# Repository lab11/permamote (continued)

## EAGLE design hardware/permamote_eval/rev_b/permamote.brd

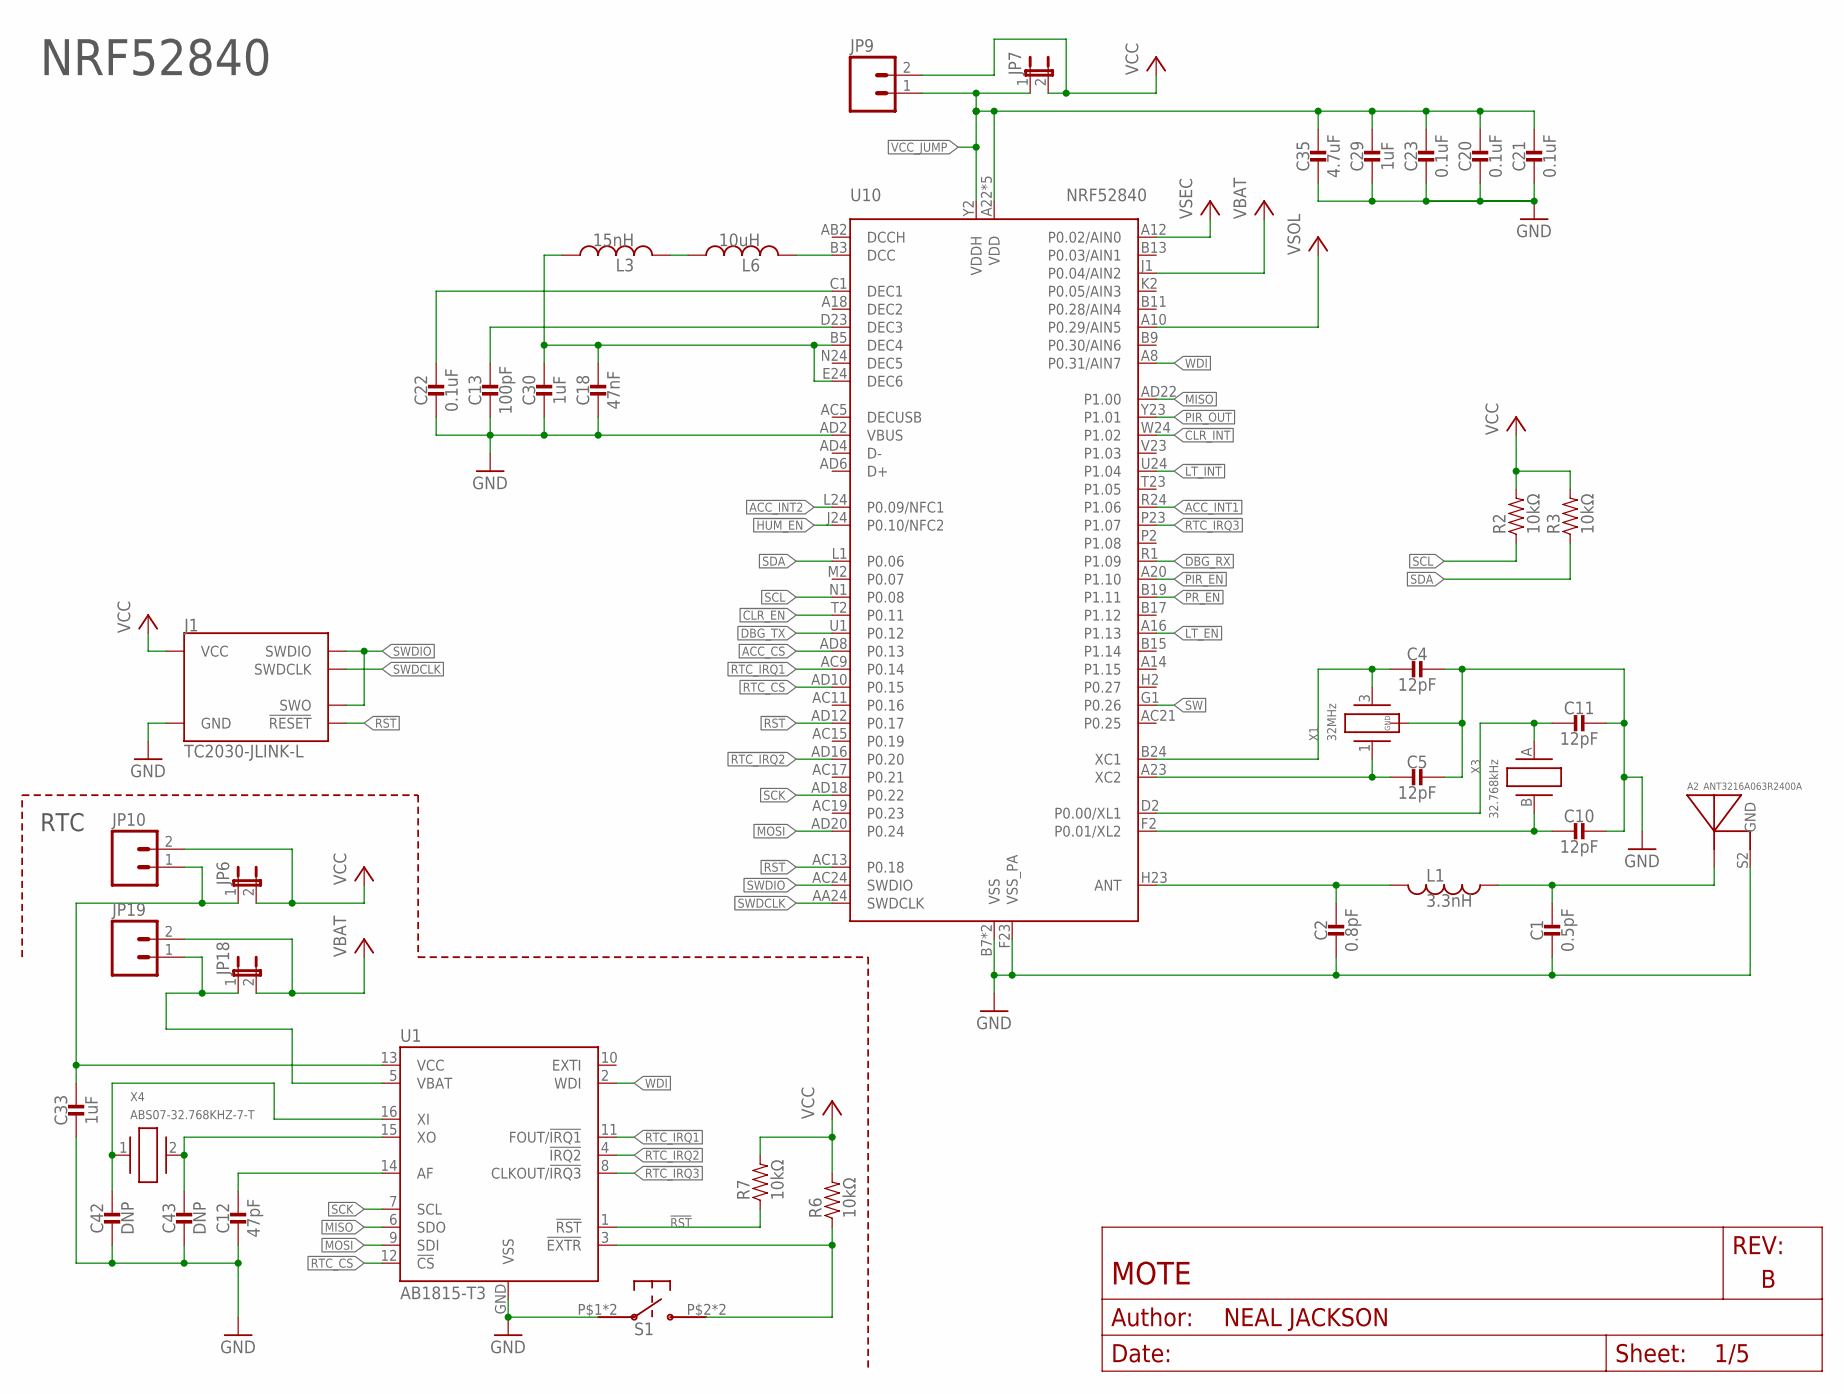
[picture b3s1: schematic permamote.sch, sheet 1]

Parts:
A2: ANT3216A063R2400A
C1: 0.5pF; 0402_CAP; DIGIKEY 490-6264-1-ND
C2: 0.8pF; 0402_CAP; DIGIKEY 490-6269-1-ND
C4, C5, C10, C11: 12pF; 0402_CAP; DIGIKEY 490-6197-1-ND
C12: 47pF; 0402_CAP; DIGIKEY 490-5942-1-ND
C13: 100pF; 0402_CAP; DIGIKEY 490-5922-1-ND
C18: 47nF; 0402_CAP; DIGIKEY 445-1264-1-ND
C20, C21, C22, C23: 0.1uF; 0402_CAP; DIGIKEY 490-6328-1-ND
C29, C30, C33: 1uF; 0402_CAP; DIGIKEY 490-7195-1-ND
C35: 4.7uF; 0402_CAP; DIGIKEY 445-5947-1-ND
C42, C43: DNP; 0402_CAP
J1: TC2030-JLINK-L; TC2030-IDC
JP6, JP7, JP18: JUMPER-2SMD-NC; SJ_2S
JP9, JP10, JP19: M02PTH; 1X02
L1: 3.3nH; 0402_CAP; DIGIKEY 535-10426-1-ND
L3: 15nH; 0402_CAP; DIGIKEY 587-1521-1-ND
L6: 10uH; 0603_CAP; DIGIKEY 490-4025-1-ND
R2, R3, R6, R7: 10kΩ; 0402_RES; DIGIKEY 311-10KJRCT-ND
S1: EVQP2
U1: AB1815-T3; QFN-16-3MM
U10: NRF52840; AQFN73
X1: 32MHz; TXC-7V
X3: 32.768kHz; ABS05
X4: ABS07-32.768KHZ-7-T; 2-SMD

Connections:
!CLR_EN: U10.T2 (P0.11); also elsewhere on the board
!CLR_INT: U10.W24 (P1.02); also elsewhere on the board
!HUM_EN: U10.J24 (P0.10/NFC2); also elsewhere on the board
!LT_EN: U10.A16 (P1.13); also elsewhere on the board
!LT_INT: U10.U24 (P1.04); also elsewhere on the board
!PIR_EN: U10.A20 (P1.10); also elsewhere on the board
!PR_EN: U10.B19 (P1.11); also elsewhere on the board
!RST: J1.3 (!RESET), R7.1, U1.1 (!RST), U10.AC13 (P0.18), U10.AD12 (P0.17); also elsewhere on the board
!RTC_EXTR: R6.1, S1.P$2, S1.P$4, U1.3 (!EXTR)
!RTC_IRQ1: U1.11 (FOUT/!IRQ1), U10.AC9 (P0.14); also elsewhere on the board
!RTC_IRQ2: U1.4 (!IRQ2), U10.AD16 (P0.20); also elsewhere on the board
!RTC_IRQ3: U1.8 (CLKOUT/!IRQ3), U10.P23 (P1.07); also elsewhere on the board
ACC_CS: U10.AD8 (P0.13); also elsewhere on the board
ACC_INT1: U10.R24 (P1.06); also elsewhere on the board
ACC_INT2: U10.L24 (P0.09/NFC1); also elsewhere on the board
DBG_RX: U10.R1 (P1.09); also elsewhere on the board
DBG_TX: U10.U1 (P0.12); also elsewhere on the board
GND: A2.S2 (GND), C1.2, C2.2, C4.1, C5.1, C10.1, C11.1, C12.2, C13.2, C18.2, C20.2, C21.2, C22.2, C23.2, C29.2, C30.2, C33.2, C35.2, C42.2, C43.2, J1.5 (GND), S1.P$1, S1.P$3, U1.GND (VSS), U10.AD2 (VBUS), U10.B7 (VSS), U10.F23 (VSS_PA), U10.GND (VSS), X1.2 (GND), X1.4 (GND); also elsewhere on the board
MISO: U1.6 (SDO), U10.AD22 (P1.00); also elsewhere on the board
MOSI: U1.9 (SDI), U10.AD20 (P0.24); also elsewhere on the board
unnamed: C22.1, U10.C1 (DEC1)
unnamed: C18.1, C30.1, L3.1, U10.B5 (DEC4), U10.E24 (DEC6)
unnamed: C13.1, U10.D23 (DEC3)
unnamed: C2.1, L1.2, U10.H23 (ANT)
unnamed: A2.S1 (ANTENNA), C1.1, L1.1
unnamed: C4.2, U10.B24 (XC1), X1.3 (2)
unnamed: C5.2, U10.A23 (XC2), X1.1
unnamed: C12.1, U1.14 (AF)
unnamed: C42.1, U1.16 (XI), X4.1
unnamed: C43.1, U1.15 (XO), X4.2
unnamed: C33.1, JP6.1, JP10.1, U1.13 (VCC)
unnamed: L6.2, U10.B3 (DCC)
unnamed: L3.2, L6.1
unnamed: JP18.1, JP19.1, U1.5 (VBAT)
PIR_OUT: U10.Y23 (P1.01); also elsewhere on the board
RTC_CS: U1.12 (!CS), U10.AD10 (P0.15); also elsewhere on the board
SCK: U1.7 (SCL), U10.AD18 (P0.22); also elsewhere on the board
SCL: R2.1, U10.N1 (P0.08); also elsewhere on the board
SDA: R3.1, U10.L1 (P0.06); also elsewhere on the board
SW: U10.G1 (P0.26); also elsewhere on the board
SWDCLK: J1.4 (SWDCLK), U10.AA24 (SWDCLK); also elsewhere on the board
SWDIO: J1.2 (SWDIO), J1.6 (SWO), U10.AC24 (SWDIO); also elsewhere on the board
VBAT: JP18.2, JP19.2, U10.J1 (P0.04/AIN2); also elsewhere on the board
VCC: J1.1 (VCC), JP6.2, JP7.2, JP9.2, JP10.2, R2.2, R3.2, R6.2, R7.2; also elsewhere on the board
VCC_JUMP: C20.1, C21.1, C23.1, C29.1, C35.1, JP7.1, JP9.1, U10.A22 (VDD), U10.AD14 (VDD), U10.AD23 (VDD), U10.B1 (VDD), U10.W1 (VDD), U10.Y2 (VDDH); also elsewhere on the board
VSEC: U10.A12 (P0.02/AIN0); also elsewhere on the board
VSOL: U10.A10 (P0.29/AIN5); also elsewhere on the board
WDI: U1.2 (WDI), U10.A8 (P0.31/AIN7); also elsewhere on the board
XL1: C11.2, U10.D2 (P0.00/XL1), X3.A (1)
XL2: C10.2, U10.F2 (P0.01/XL2), X3.B (2)

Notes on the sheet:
NRF52840
RTC

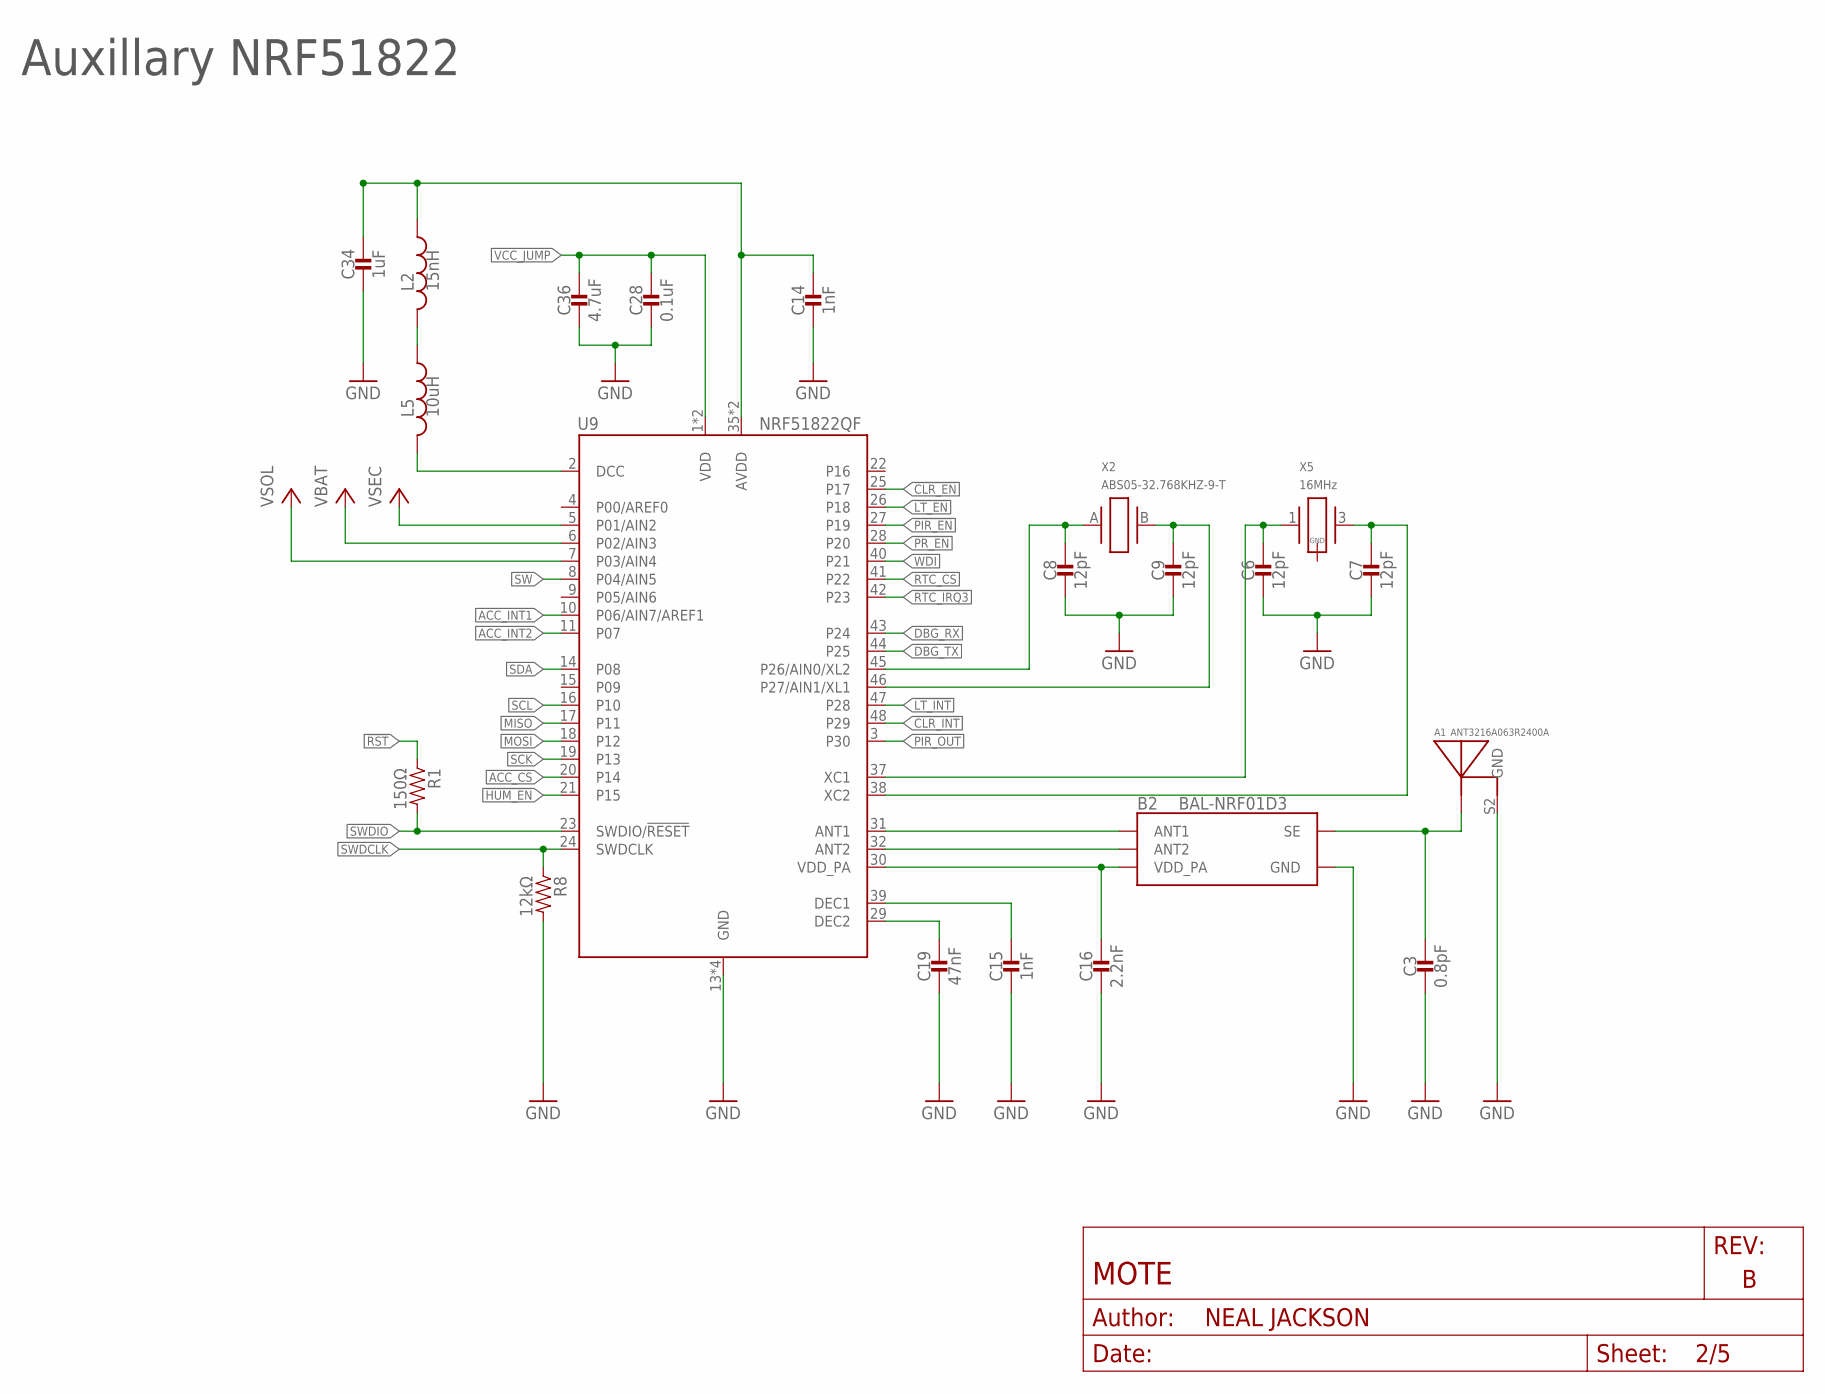
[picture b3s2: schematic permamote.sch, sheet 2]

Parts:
A1: ANT3216A063R2400A
B2: BAL-NRF01D3
C3: 0.8pF; 0402_CAP; DIGIKEY 490-6269-1-ND
C6, C7, C8, C9: 12pF; 0402_CAP; DIGIKEY 490-6197-1-ND
C14, C15: 1nF; 0402_CAP; DIGIKEY 490-1303-1-ND
C16: 2.2nF; 0402_CAP; DIGIKEY 490-5419-1-ND
C19: 47nF; 0402_CAP; DIGIKEY 445-1264-1-ND
C28: 0.1uF; 0402_CAP; DIGIKEY 490-6328-1-ND
C34: 1uF; 0402_CAP; DIGIKEY 490-7195-1-ND
C36: 4.7uF; 0402_CAP; DIGIKEY 445-5947-1-ND
L2: 15nH; 0402_CAP; DIGIKEY 587-1521-1-ND
L5: 10uH; 0603_CAP; DIGIKEY 490-4025-1-ND
R1: 150Ω; 0402_RES; DIGIKEY 311-150JRCT-ND
R8: 12kΩ; 0402_RES; DIGIKEY RHM12.0KCDCT-ND
U9: NRF51822QF; QFN-48-6MM
X2: ABS05-32.768KHZ-9-T; ABS05
X5: 16MHz; TXC-8Y; DIGIKEY 887-2003-1-ND

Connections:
!CLR_EN: U9.25 (P17); also elsewhere on the board
!CLR_INT: U9.48 (P29); also elsewhere on the board
!HUM_EN: U9.21 (P15); also elsewhere on the board
!LT_EN: U9.26 (P18); also elsewhere on the board
!LT_INT: U9.47 (P28); also elsewhere on the board
!PIR_EN: U9.27 (P19); also elsewhere on the board
!PR_EN: U9.28 (P20); also elsewhere on the board
!RST: R1.1; also elsewhere on the board
!RTC_IRQ3: U9.42 (P23); also elsewhere on the board
ACC_CS: U9.20 (P14); also elsewhere on the board
ACC_INT1: U9.10 (P06/AIN7/AREF1); also elsewhere on the board
ACC_INT2: U9.11 (P07); also elsewhere on the board
AVDD1: C14.1, C34.1, L2.1, U9.35 (AVDD), U9.36 (AVDD)
DBG_RX: U9.43 (P24); also elsewhere on the board
DBG_TX: U9.44 (P25); also elsewhere on the board
DCC1: L5.2, U9.2 (DCC)
GND: A1.S2 (GND), B2.GND, C3.2, C6.2, C7.2, C8.2, C9.2, C14.2, C15.2, C16.2, C19.2, C28.2, C34.2, C36.2, R8.2, U9.13 (GND), U9.33 (GND), U9.34 (GND), U9.GND; also elsewhere on the board
MISO: U9.17 (P11); also elsewhere on the board
MOSI: U9.18 (P12); also elsewhere on the board
unnamed: B2.ANT1, U9.31 (ANT1)
unnamed: B2.ANT2, U9.32 (ANT2)
unnamed: A1.S1 (ANTENNA), B2.SE, C3.1
unnamed: L2.2, L5.1
unnamed: C6.1, U9.37 (XC1), X5.1
unnamed: C7.1, U9.38 (XC2), X5.3 (2)
unnamed: C15.1, U9.39 (DEC1)
unnamed: C19.1, U9.29 (DEC2)
NRF_A2: C9.1, U9.46 (P27/AIN1/XL1), X2.B (2)
NRF_A3: C8.1, U9.45 (P26/AIN0/XL2), X2.A (1)
PIR_OUT: U9.3 (P30); also elsewhere on the board
RTC_CS: U9.41 (P22); also elsewhere on the board
SCK: U9.19 (P13); also elsewhere on the board
SCL: U9.16 (P10); also elsewhere on the board
SDA: U9.14 (P08); also elsewhere on the board
SW: U9.8 (P04/AIN5); also elsewhere on the board
SWDCLK: R8.1, U9.24 (SWDCLK); also elsewhere on the board
SWDIO: R1.2, U9.23 (SWDIO/!RESET); also elsewhere on the board
VBAT: U9.6 (P02/AIN3); also elsewhere on the board
VCC_JUMP: C28.1, C36.1, U9.1 (VDD), U9.12 (VDD); also elsewhere on the board
VDD_PA1: B2.VCC (VDD_PA), C16.1, U9.30 (VDD_PA)
VSEC: U9.5 (P01/AIN2); also elsewhere on the board
VSOL: U9.7 (P03/AIN4); also elsewhere on the board
WDI: U9.40 (P21); also elsewhere on the board

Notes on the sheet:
Auxillary NRF51822

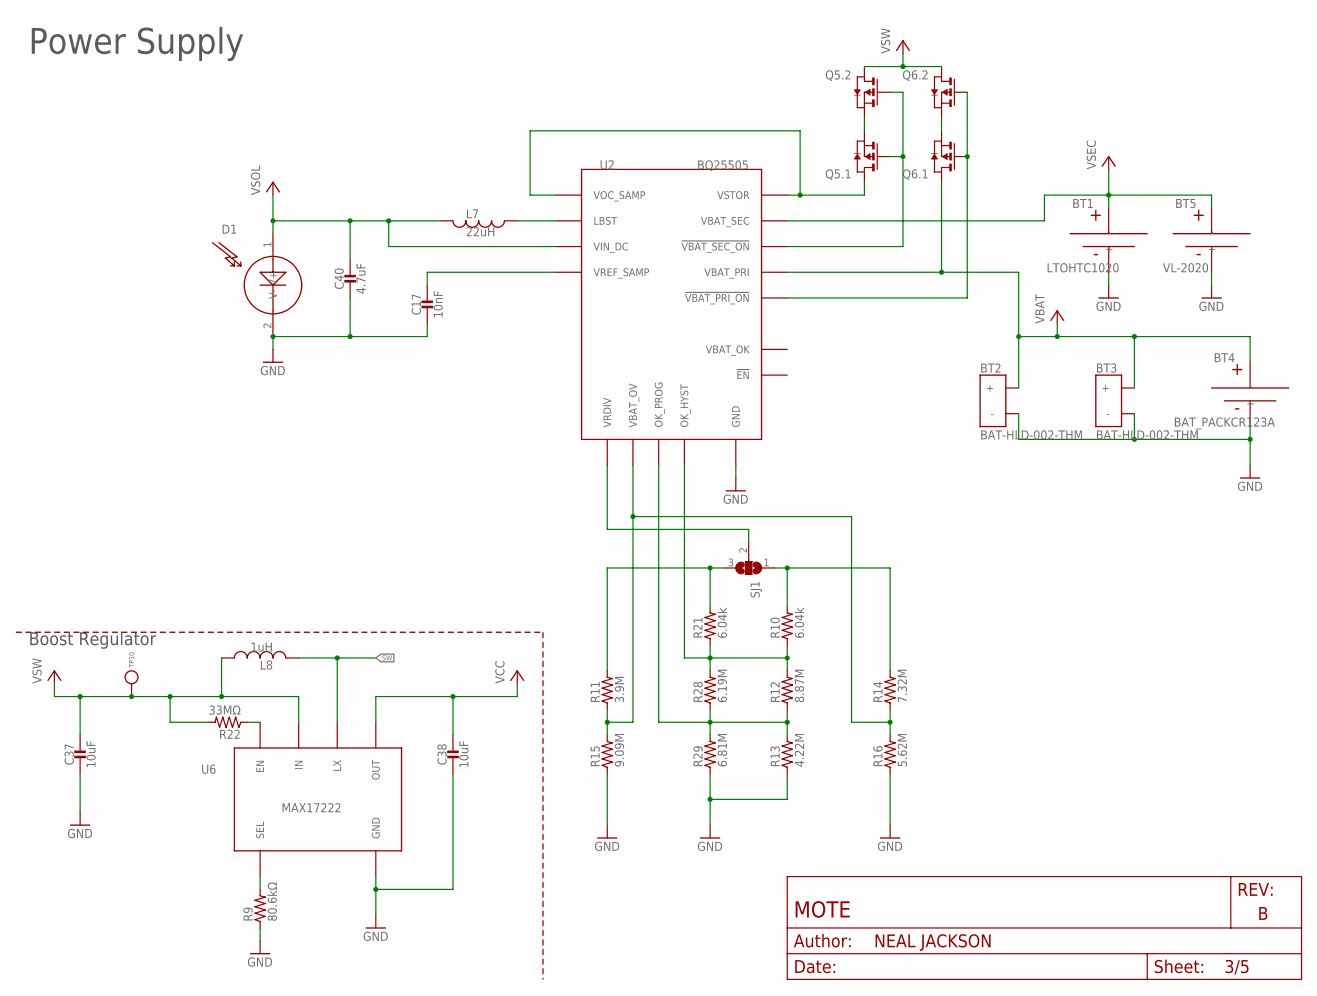
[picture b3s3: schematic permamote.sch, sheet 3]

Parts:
BT1: LTOHTC1020; 1020
BT2, BT3: BAT-HLD-002-THM
BT4: BAT_PACKCR123A; BH123A
BT5: VL-2020
C17: 10nF; 0402_CAP; DIGIKEY 490-4516-1-ND
C37, C38: 10uF; 0603_CAP; DIGIKEY 490-3896-1-ND
C40: 4.7uF; 0603_CAP; DIGIKEY 490-3896-1-ND
D1: SOLARCELLSCREW; PHEONIX-1935161
L7: 22uH; 74437324220; DIGIKEY 732-3340-1-ND
L8: 1uH; IHL-1212BZ-11; MPN IHLP1212BZER1R0M11; DIGIKEY 541-1319-1-ND
Q5, Q6: PMDXB950UPEL; XDFN-6
R9: 80.6kΩ; 0603-RES; DIGIKEY 311-80.6KHRCT-ND
R10, R21: 6.04k; 0402_RES; DIGIKEY YAG3306CT-ND
R11: 3.9M; 0402_RES; DIGIKEY YAG3306CT-ND
R12: 8.87M; 0402_RES; DIGIKEY YAG3306CT-ND
R13: 4.22M; 0402_RES; DIGIKEY YAG3306CT-ND
R14: 7.32M; 0402_RES; DIGIKEY YAG3306CT-ND
R15: 9.09M; 0402_RES; DIGIKEY YAG3306CT-ND
R16: 5.62M; 0402_RES; DIGIKEY YAG3306CT-ND
R22: 33MΩ; 0603-RES; DIGIKEY HMC0603JT33M0CT-ND
R28: 6.19M; 0402_RES; DIGIKEY YAG3306CT-ND
R29: 6.81M; 0402_RES; DIGIKEY YAG3306CT-ND
SJ1: SJ2W; SJ_2
TP10: TEST_POINT_0.040IN; TESTPOINT_0.040IN
U2: BQ25505; S-PVQFN-N20-RGR
U6: MAX17222; UDFN-6-MAXIM

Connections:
!VBAT_PRI_ON: Q6.2 (G), Q6.5 (G), U2.10 (!VBAT_PRI_ON)
!VBAT_SEC_ON: Q5.2 (G), Q5.5 (G), U2.9 (!VBAT_SEC_ON)
GND: BT1.-, BT2.GND (-), BT3.GND (-), BT4.-, BT5.-, C17.2, C37.2, C38.2, C40.2, D1.2 (V-), R9.1, R13.1, R15.1, R16.1, R29.1, U2.1 (GND), U2.6 (GND), U2.15 (GND), U2.16 (GND), U2.17 (GND), U2.PAD (GND), U6.3 (GND); also elsewhere on the board
unnamed: R11.2, R21.2, SJ1.3
unnamed: R9.2, U6.4 (SEL)
unnamed: R22.1, U6.6 (EN)
unnamed: R10.2, R14.2, SJ1.1
unnamed: R11.1, R14.1, R15.2, R16.2, U2.7 (VBAT_OV)
unnamed: C17.1, U2.4 (VREF_SAMP)
unnamed: SJ1.2, U2.8 (VRDIV)
unnamed: L7.P$1 (1), U2.20 (LBST)
unnamed: Q5.1 (S), Q5.4 (S)
unnamed: Q5.6 (D), U2.3 (VOC_SAMP), U2.19 (VSTOR)
unnamed: Q6.1 (S), Q6.4 (S)
unnamed: R12.1, R13.2, R28.1, R29.2, U2.12 (OK_PROG)
unnamed: R10.1, R12.2, R21.1, R28.2, U2.11 (OK_HYST)
SW: L8.P$2 (2), U6.2 (LX); also elsewhere on the board
VBAT: BT2.POS1 (+), BT2.POS2 (+), BT2.POS3 (+), BT2.POS4 (+), BT3.POS1 (+), BT3.POS2 (+), BT3.POS3 (+), BT3.POS4 (+), BT4.+, Q6.6 (D), U2.14 (VBAT_PRI); also elsewhere on the board
VCC: C38.1, U6.1 (OUT); also elsewhere on the board
VSEC: BT1.+, BT5.+, U2.18 (VBAT_SEC); also elsewhere on the board
VSOL: C40.1, D1.1 (V+), L7.P$2 (2), U2.2 (VIN_DC); also elsewhere on the board
VSW: C37.1, L8.P$1 (1), Q5.3 (D), Q6.3 (D), R22.2, TP10.TESTPOINT, U6.5 (IN)

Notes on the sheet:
Power Supply
Boost Regulator

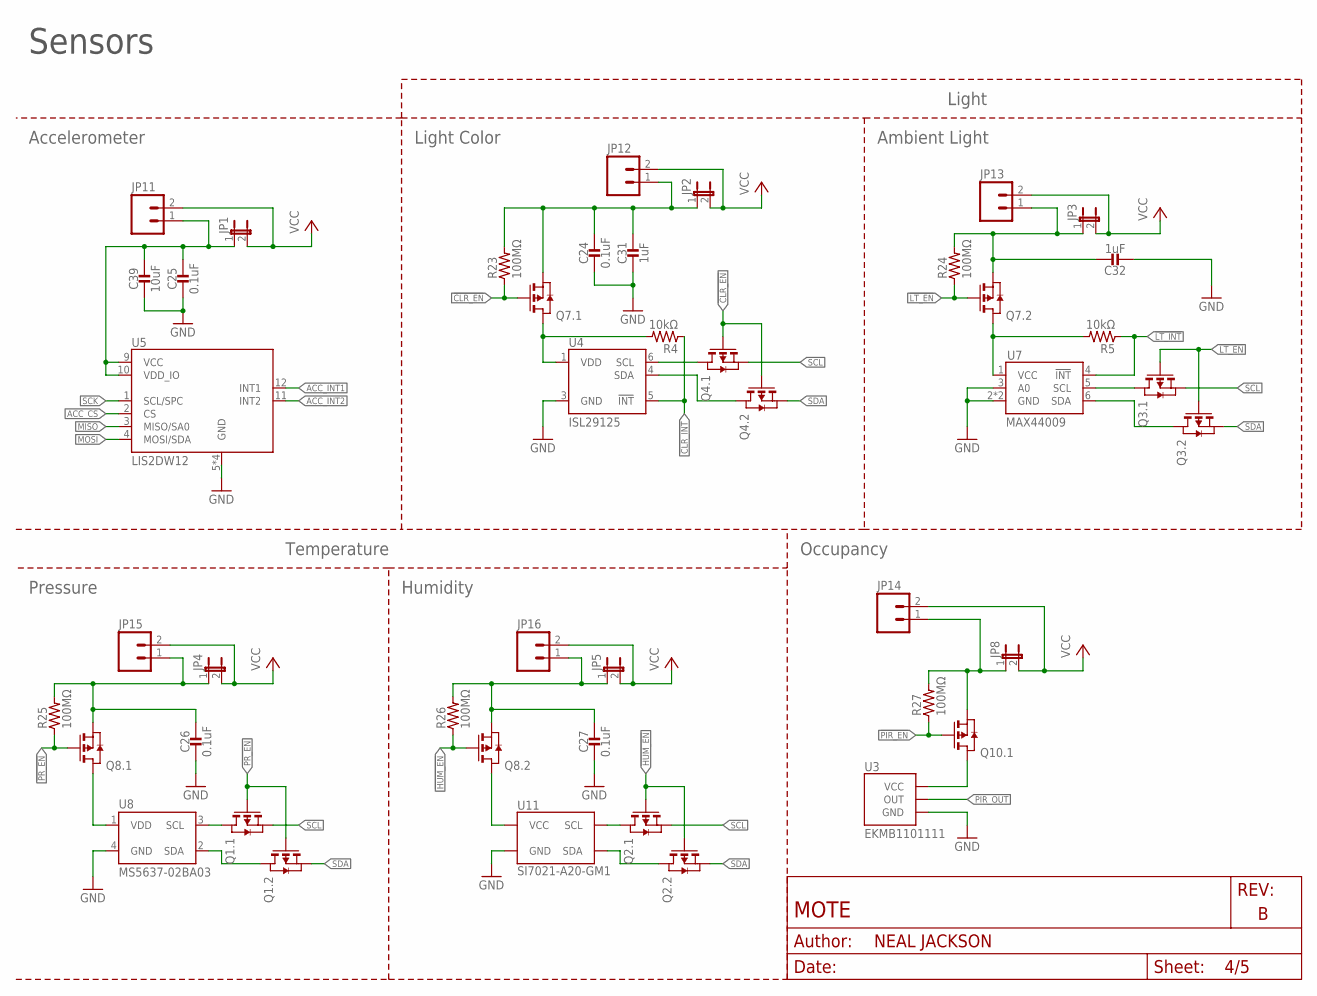
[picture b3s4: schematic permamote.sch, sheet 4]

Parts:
C24, C25, C26, C27: 0.1uF; 0402_CAP; DIGIKEY 490-6328-1-ND
C31, C32: 1uF; 0402_CAP; DIGIKEY 490-7195-1-ND
C39: 10uF; 0603_CAP; DIGIKEY 490-3896-1-ND
JP1, JP2, JP3, JP4, JP5, JP8: JUMPER-2SMD-NC; SJ_2S
JP11, JP12, JP13, JP14, JP15, JP16: M02PTH; 1X02
Q1, Q2, Q3, Q4, Q7, Q8, Q10: PMDXB950UPEL; XDFN-6
R4, R5: 10kΩ; 0402_RES; DIGIKEY 311-10KJRCT-ND
R23, R24, R25, R26, R27: 100MΩ; 0402_RES; DIGIKEY 541-100MAHCT-ND
U3: EKMB1101111; AMN2
U4: ISL29125; ODFN-6-1.5MMX1.6MM
U5: LIS2DW12; LGA-12
U7: MAX44009; UDFN-6-EXPOSED
U8: MS5637-02BA03; 4-SMD
U11: SI7021-A20-GM1; DFN-6/3MM

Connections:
!CLR_EN: Q4.2 (G), Q4.5 (G), Q7.2 (G), R23.1; also elsewhere on the board
!CLR_INT: R4.1, U4.5 (!INT); also elsewhere on the board
!HUM_EN: Q2.2 (G), Q2.5 (G), Q8.5 (G), R26.1; also elsewhere on the board
!LT_EN: Q3.2 (G), Q3.5 (G), Q7.5 (G), R24.1; also elsewhere on the board
!LT_INT: R5.1, U7.4 (!INT); also elsewhere on the board
!PIR_EN: Q10.2 (G), R27.1; also elsewhere on the board
!PR_EN: Q1.2 (G), Q1.5 (G), Q8.2 (G), R25.1; also elsewhere on the board
ACC_CS: U5.2 (CS); also elsewhere on the board
ACC_INT1: U5.12 (INT1); also elsewhere on the board
ACC_INT2: U5.11 (INT2); also elsewhere on the board
GND: C24.2, C25.2, C26.2, C27.2, C31.2, C32.2, C39.2, U3.GND, U4.3 (GND), U5.5 (GND), U5.6 (GND), U5.7 (GND), U5.8 (GND), U7.2 (GND), U7.3 (A0), U7.EP (GND), U8.4 (GND), U11.2 (GND); also elsewhere on the board
MISO: U5.3 (MISO/SA0); also elsewhere on the board
MOSI: U5.4 (MOSI/SDA); also elsewhere on the board
unnamed: C25.1, C39.1, JP1.1, JP11.1, U5.9 (VCC), U5.10 (VDD_IO)
unnamed: C26.1, JP4.1, JP15.1, Q8.1 (S), R25.2
unnamed: Q8.6 (D), U8.1 (VDD)
unnamed: Q8.3 (D), U11.5 (VCC)
unnamed: Q10.6 (D), U3.VCC
unnamed: JP8.1, JP14.1, Q10.1 (S), R27.2
unnamed: Q7.6 (D), R4.2, U4.1 (VDD)
unnamed: C24.1, C31.1, JP2.1, JP12.1, Q7.1 (S), R23.2
unnamed: Q1.6 (D), U8.3 (SCL)
unnamed: C27.1, JP5.1, JP16.1, Q8.4 (S), R26.2
unnamed: C32.1, JP3.1, JP13.1, Q7.4 (S), R24.2
unnamed: Q1.3 (D), U8.2 (SDA)
unnamed: Q2.3 (D), U11.1 (SDA)
unnamed: Q2.6 (D), U11.6 (SCL)
unnamed: Q3.3 (D), U7.6 (SDA)
unnamed: Q3.6 (D), U7.5 (SCL)
unnamed: Q4.3 (D), U4.4 (SDA)
unnamed: Q4.6 (D), U4.6 (SCL)
unnamed: Q7.3 (D), R5.2, U7.1 (VCC)
PIR_OUT: U3.OUT; also elsewhere on the board
SCK: U5.1 (SCL/SPC); also elsewhere on the board
SCL: Q1.1 (S), Q2.1 (S), Q3.1 (S), Q4.1 (S); also elsewhere on the board
SDA: Q1.4 (S), Q2.4 (S), Q3.4 (S), Q4.4 (S); also elsewhere on the board
VCC: JP1.2, JP2.2, JP3.2, JP4.2, JP5.2, JP8.2, JP11.2, JP12.2, JP13.2, JP14.2, JP15.2, JP16.2; also elsewhere on the board

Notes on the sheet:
Sensors
Accelerometer
Temperature
Humidity
Pressure
Ambient Light
Light Color
Light
Occupancy

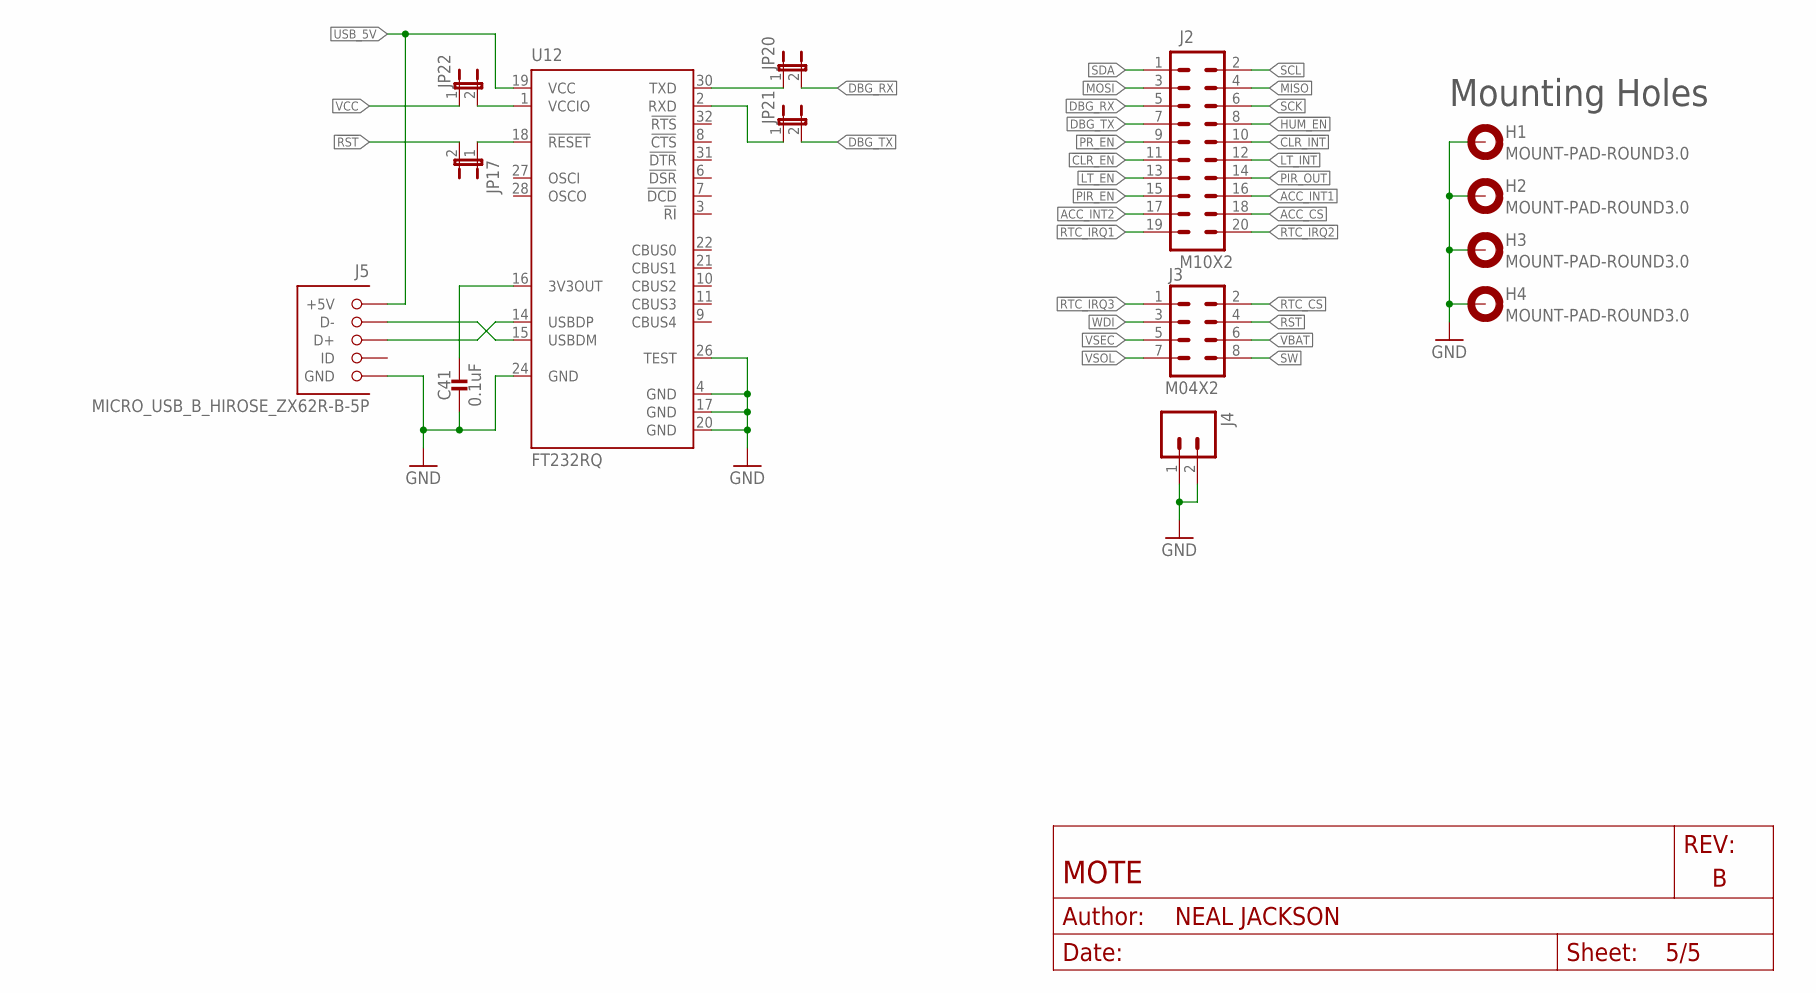
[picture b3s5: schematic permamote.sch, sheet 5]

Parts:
C41: 0.1uF; 0402_CAP; DIGIKEY 490-6328-1-ND
H1, H2, H3, H4: MOUNT-PAD-ROUND3.0; 3,0-PAD
J2: M10X2; 2X10
J3: M04X2; 2X4
J4: M02PTH; 1X02
J5: MICRO_USB_B_HIROSE_ZX62R-B-5P; USB_MICRO_B-HIROSE-ZX62R-B-5P
JP17: JUMPER-2SMD-NO; SJ_2S-NO
JP20, JP21, JP22: JUMPER-2SMD-NC; SJ_2S
U12: FT232RQ; QFN32

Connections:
3V3OUT: C41.1, U12.16 (3V3OUT)
!CLR_EN: J2.11; also elsewhere on the board
!CLR_INT: J2.10; also elsewhere on the board
!HUM_EN: J2.8; also elsewhere on the board
!LT_EN: J2.13; also elsewhere on the board
!LT_INT: J2.12; also elsewhere on the board
!PIR_EN: J2.15; also elsewhere on the board
!PR_EN: J2.9; also elsewhere on the board
!RST: J3.4, JP17.2; also elsewhere on the board
!RTC_IRQ1: J2.19; also elsewhere on the board
!RTC_IRQ2: J2.20; also elsewhere on the board
!RTC_IRQ3: J3.1; also elsewhere on the board
ACC_CS: J2.18; also elsewhere on the board
ACC_INT1: J2.16; also elsewhere on the board
ACC_INT2: J2.17; also elsewhere on the board
D+: J5.3 (D+), U12.14 (USBDP)
D-: J5.2 (D-), U12.15 (USBDM)
DBG_RX: J2.5, JP20.2; also elsewhere on the board
DBG_TX: J2.7, JP21.2; also elsewhere on the board
GND: C41.2, H1.B3,0, H2.B3,0, H3.B3,0, H4.B3,0, J4.1, J4.2, J5.5 (GND), U12.4 (GND), U12.17 (GND), U12.20 (GND), U12.24 (GND), U12.26 (TEST); also elsewhere on the board
MISO: J2.4; also elsewhere on the board
MOSI: J2.3; also elsewhere on the board
unnamed: JP22.2, U12.1 (VCCIO)
unnamed: JP17.1, U12.18 (!RESET)
PIR_OUT: J2.14; also elsewhere on the board
RTC_CS: J3.2; also elsewhere on the board
RXD: JP21.1, U12.2 (RXD)
SCK: J2.6; also elsewhere on the board
SCL: J2.2; also elsewhere on the board
SDA: J2.1; also elsewhere on the board
SW: J3.8; also elsewhere on the board
TXD: JP20.1, U12.30 (TXD)
USB_5V: J5.1 (+5V), U12.19 (VCC)
VBAT: J3.6; also elsewhere on the board
VCC: JP22.1; also elsewhere on the board
VSEC: J3.5; also elsewhere on the board
VSOL: J3.7; also elsewhere on the board
WDI: J3.3; also elsewhere on the board

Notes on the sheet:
Mounting Holes

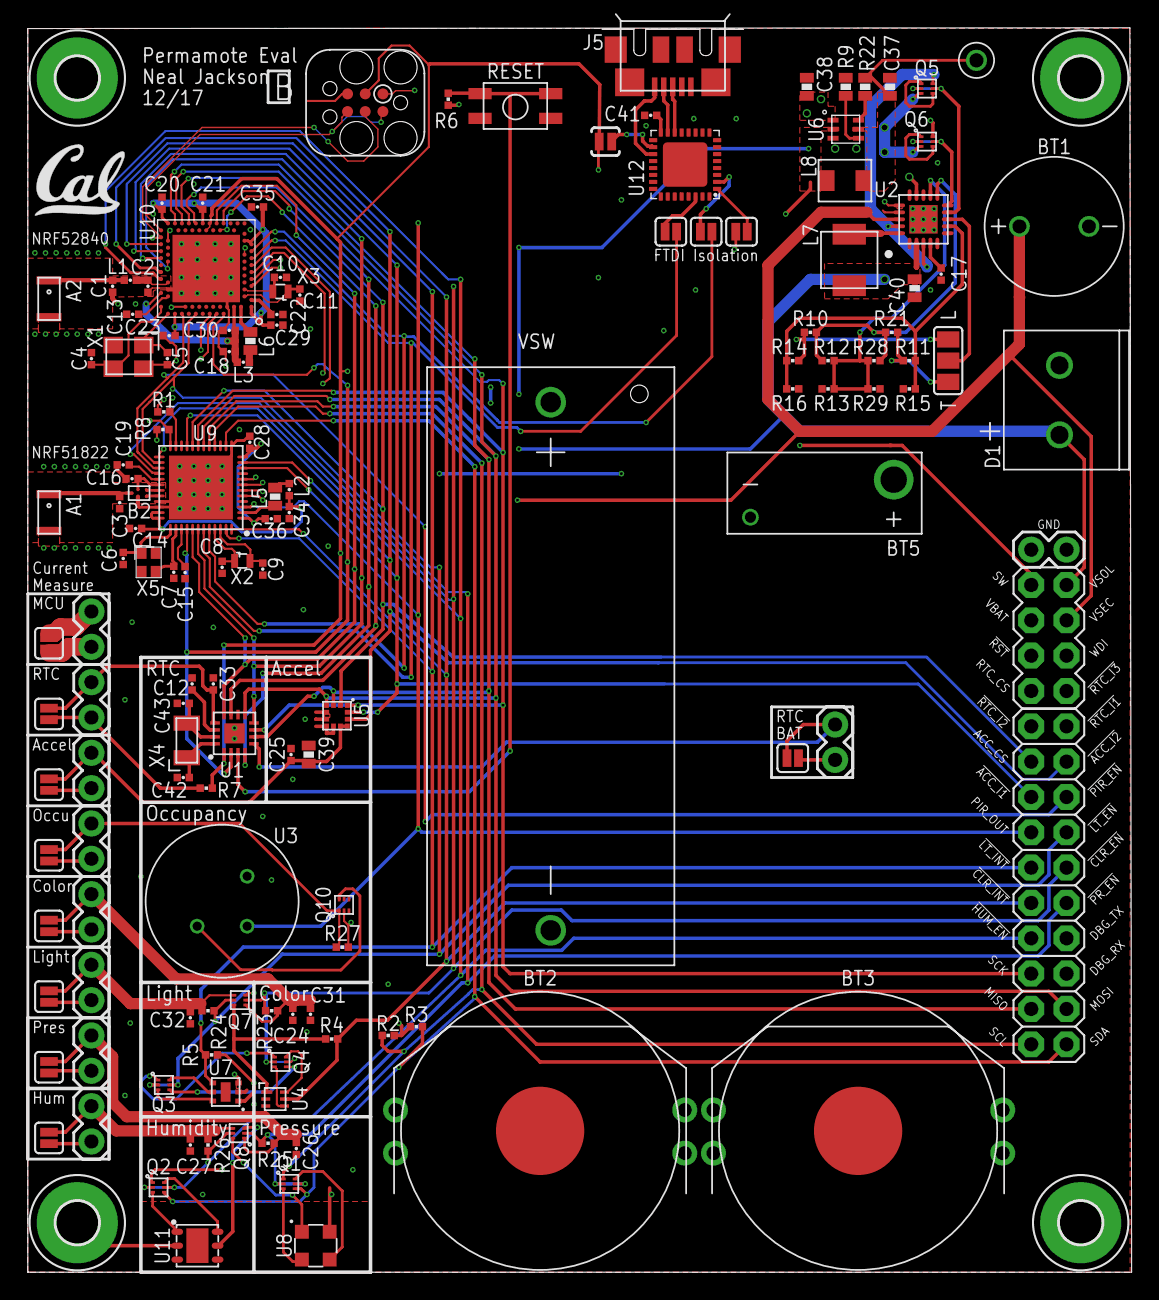
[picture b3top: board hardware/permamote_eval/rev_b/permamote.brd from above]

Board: 4 copper layers, 79.4 x 89.5 mm, 145 parts (0 on the bottom side), 106 nets.

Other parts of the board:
U$1: UCB_CAL_200MIL
